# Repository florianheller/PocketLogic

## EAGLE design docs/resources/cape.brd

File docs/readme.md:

# Introduction
This is a documentation on how to use a [PocketBeagle](http://beagleboard.org/pocket) board to drive a [PlasticLogic](http://www.plasticlogic.com) ePaper display. 
I implemented a wearable prototype based on the 4.9" Lectum Display and started with the PlasticLogic [Ruddock 2](http://www.plasticlogic.com/products/evaluation-kits/kits-on-epson-platform/kits-4-9-inch-display/#1503061380699-f800df99-5e01) evaluation board. 
However, since my prototype was designed to be a wearable device, I had to move to a smaller form factor. 
As the platform is quite general-purpose, I share the information such that you can build your own one. 

# Prerequisites
For this tutorial I used the following hardware:
- PocketBeagle board ([link](http://beagleboard.org/pocket))
- 16Gb microSD-card (everything with 4Gb or more should do fine)
- PlasticLogic Hummingbird Z7.2 EPD Driver Board (C_HBZ7 / 301015) ([link](http://www.plasticlogic.com/products/evaluation-kits/kits-on-epson-platform/kits-4-9-inch-display/#1503061380699-f800df99-5e01))
- PlasticLogic 4.9" Lectum ePaper Display ([link](https://www.plasticlogic.com/products/displays/displays-with-epson/4-9-inch-display/))

This tutorial should work with all Epson S1D13541 EPD controller-based displays that are powered using the Hummingbird Z7.2 controller and connected using the 24-pin FPC connector. If in doubt, ask PlasticLogic first.  

# The Board
## Schematics 

[cape.sch](./resources/cape.sch)

## Board

[cape.brd](./resources/cape.brd)

I had my boards being manufactured by [Aisler](https://aisler.net). 

## BOM

| Part | Digikey Order Number |
| ---- | --- |
| XF2M-2415-1A  |  OR721CT-ND |
| USB			|  ED2989-ND  |
| R1, R2		|  RHM22DCT-ND|
| RNx			| 741X083101JPCT-ND|

# Preparing the PocketBeagle

First of all, you need to get you PocketBeagle running by flashing Linux onto a microSD card. 
Download the latest Debian image from the [beagleboard.org](http://beagleboard.org/latest-images) website. As the PocketBeagle does not have video output, we'll use the IoT-version without graphical desktop.
At the time of writing of this tutorial, the latest version was "Debian 9.5 2018-10-07 4GB SD IoT"

To flash the image, I use [Etcher](https://www.balena.io/etcher/). Just select the image and flash it onto your microSD card (all data on that card will be lost!). 

Once the OS is flashed, insert the microSD card into your PocketBeagle and connect it to your computer. On my Mac, it is reachable through IPs 192.168.6.2 or 192.168.7.2

SSH into your PocketBeagle using 
```ssh debian@192.168.7.2```
The default password is `temppwd' which you should change obviously.
 
### Optional: Re-partition the microSD-card to use its full capacity
The beagleboard images are set up to fit exactly on a 4Gb card. If you flash it onto a larger card, the remaining space will be left unused. 
If you want to use the additional space, you need to re-partition the card accordingly. See [this guide](https://elinux.org/Beagleboard:Expanding_File_System_Partition_On_A_microSD) for more info. 

### Install the required packages
```sudo apt-get install libfreetype6 ```

## Setting the pins to their intended use
The pins on the PocketBeagle can serve multiple purposes, from general purpose I/O to specific hardware capabilities. Their functionality is controlled through the config-pin command. For example, the Pin P1_08, which we will use for the SPI_CLK signal can have the following functionality:

```
debian@beaglebone:~$ config-pin -i P1_08
Pin name: P1_08
Function if no cape loaded: spi_sclk
Function if cape loaded: default gpio gpio_pu gpio_pd gpio_input spi_sclk uart i2c pwm pru_uart
Function information: spi0_sclk default gpio0_2 gpio0_2 gpio0_2 gpio0_2 spi0_sclk uart2_rxd i2c2_sda ehrpwm0a pru_uart
Kernel GPIO id: 2
PRU GPIO id: 34
```

To set the pins to their correct purpose automatically at boot time, we will use the same procedure as described [here](https://gist.github.com/pdp7/d4770a6ba17e666848796bf5cfd0caee)

## Configure pins at boot time

Create a file `/usr/bin/epdc-enable-pins.sh`

**sudo nano /usr/bin/epdc-enable-pins.sh**
```bash
#!/bin/bash
#EPDC Connector
config-pin P1_08 spi_sclk	#SPI_CLK
config-pin P1_10 spi		#SPI_MISO
config-pin P1_12 spi		#SPI_MOSI
config-pin P1_20 in			#HRDY
config-pin p1_32 in			#PMIC_POK
config-pin p1_33 in			#PMIC_FLT
config-pin p1_34 hi			#3V3_ENABLE
config-pin p1_36 lo			#BB_SLEEP

config-pin p2_08 hi			#HD/C
config-pin p2_09 i2c		#SCL
config-pin p2_10 hi			#SPI_CS
config-pin p2_11 i2c		#SDA
config-pin p2_17 hi			#RST
config-pin p2_18 hi+		#HIRQ
config-pin p2_19 lo			#PMIC_EN
config-pin p2_20 lo			#HVSW_CTRL

```

**sudo chmod 755 /usr/bin/epdc-enable-pins.sh**

Create a system service file `/lib/systemd/system/epdc-enable-pins.service`

**sudo nano /lib/systemd/system/epdc-enable-pins.service**
```
[Unit]
Description=Enable pins required for the ePaper display
After=generic-board-startup.service

[Service]
Type=simple
ExecStart=/usr/bin/epdc-enable-pins.sh

[Install]
WantedBy=multi-user.target
```
### Enable the new systemd service
**sudo systemctl daemon-reload**

**sudo systemctl enable epdc-enable-pins.service**

```
Created symlink /etc/systemd/system/multi-user.target.wants/epdc-enable-pins.service → /lib/systemd/system/epdc-enable-pins.service.
```

### Reboot and test
**sudo systemctl status epdc-enable-pins.service**
```
● epdc-enable-pins.service - Enable pins required for the ePaper display
   Loaded: loaded (/lib/systemd/system/epdc-enable-pins.service; enabled; vendor preset: enabled)
   Active: inactive (dead) since Sun 2018-10-07 16:41:02 UTC; 36s ago
  Process: 1531 ExecStart=/usr/bin/epdc-enable-pins.sh (code=exited, status=0/SUCCESS)
 Main PID: 1531 (code=exited, status=0/SUCCESS)

Oct 07 16:41:00 beaglebone systemd[1]: Started Enable pins required for the ePaper display.
```

# Copy the necessary configuration files
The epdc-app looks for the configuration files in the ```/boot/uboot```-folder. Depending on your configuration it might be more useful to place the files somewhere else and use softlinks (`ln -s`).
I copied the S049_T1.1 folder from this [Plastic Logic Repository)[https://github.com/plasticlogic/pl-bb-sd-card] and the following configuration files to /boot/uboot/: 

**`/boot/uboot/config.txt`**
```
display_type S049_T1.1

```

**`/boot/uboot/S049_T1.1/epdc.config`**
```
[version]
name = CONFIG_S049_T1.1

[display]
nvm = S1D13541
nvm_format = S1D13541
controller = S1D13541
temp_mode = MANUAL
instruction_code_file = "/boot/uboot/S049_T1.1/bin/Ecode.bin"
default_vcom = 4000
default_temp = 23
default_waveform = "/boot/uboot/S049_T1.1/display/waveform.bin"

[general]
driver_board = CHIFFCHAFF
control_system = BEAGLEBONE_BLACK
spi_port = 1
epdc_spi_port = 1
nvm_spi_port = 1
DISPLAY_SCRAMBLE_CONFIG	= 96

[vcom]
dac_x1				= 127	;   /* first DAC register value (25% of full scale) */
dac_y1				= 4172	;   /* corresponding first voltage in mV */
dac_x2				= 382	;   /* second DAC register value (75% of full scale) */
dac_y2				= 12490	;   /* corresponding second voltage in mV */
vgpos_mv 			= 25080	;   /* VGPOS in mV */
vgneg_mv 			=-32300	;   /* VGNEG in mV */
swing_ideal 	= 56886

[hv_hardware]
hv_config_vgl = -32300
hv_config_vgh =  25080
hv_config_vsh =  15000
vcom_driver = NULL
vcom_config = TPS65185
hv_driver = GPIO
hv_config = TPS65185
hv_timing = TPS65185
vcom_switch = GPIO
TOFFSET_VGL_ON	=	8
TOFFSET_VSL_ON	=	2
TOFFSET_VSH_ON	=	11
TOFFSET_VGH_ON	=	3
TOFFSET_VGH_OFF	=	0
TOFFSET_VSH_OFF	=	0
TOFFSET_VSL_OFF	=	0
TOFFSET_VGL_OFF	=	0
```

# Install the EPDC-App compiled for the PocketBeagle
Check the [pl-bb-epd companion repository](https://github.com/florianheller/pl-bb-epd/) for the latest version.
You can download a pre-compiled version that works on the Debian 9.5 image mentioned at the beginning of this document. [epdc-app](./resources/epdc-app)
## Test it

```
debian@beaglebone:~$ ./epdc-app -start_epdc 0 1
configparser     DISPLAYTYPE: S049_T1.1
configparser     version - CONFIG_S049_T1.1

configparser     Interface: SPI
s1d13541_controller Using HDC GPIO
configparser     No register settings specified in the configuration file.
main             load_nvm_content?: 0
s1d135xx         Product code: 0x0053
s1d13541_controller Ready 360x240
generic_epdc     epdc_init: stat: 0
tps65185         Version: 1.2.5
tps65185         tps65185_apply_timings - not yet implemented
nvm              Used nvm format (1) does not support load waveform from nvm.
generic_epdc     NVM_FORMAT_S1D13541 does not support Wf loading from NVM
generic_epdc     Loading wflib: /boot/uboot/S049_T1.1/display/waveform.bin
generic_epdc     epdc_init: stat: 0
generic_epdc     Setting vcom: 4000
vcom             input: 4000, scaled: 4035, DAC reg: 0x7B
tps65185         calculate: 4000, 123
generic_epdc     epdc_init: stat: 0
generic_epdc     do_clear_update: stat: 0
generic_epdc     switch_hvs_on: stat: 0
generic_epdc     do_clear_update: stat: 0
generic_epdc     do_clear_update: stat: 0
generic_epdc     do_clear_update: stat: 0
generic_epdc     switch_hvs_off: stat: 0
generic_epdc     do_clear_update: stat: 0
```

## Update an image on the display
```
debian@beaglebone:~$ ./epdc-app -update_image /boot/uboot/S049_T1.1/img/dresden.png
configparser     DISPLAYTYPE: S049_T1.1
configparser     version - CONFIG_S049_T1.1

configparser     Interface: SPI
s1d13541_controller Using HDC GPIO
configparser     No register settings specified in the configuration file.
main             path: /boot/uboot/S049_T1.1/img/dresden.png
main             wfID: 1
main             updateMode: 0
main             updateCount: 1
main             waitTime: 0
main             vcomSwitch: 1
s1d135xx         BW
utils            filename /boot/uboot/S049_T1.1/img/dresden.png
utils            width 720, height 120, bit_depth 8, channels 1
generic_epdc     generic_update: stat: 0
generic_epdc     generic_update: stat: 0
generic_epdc     switch_hvs_on: stat: 0
generic_epdc     generic_update: stat: 0
generic_epdc     generic_update: stat: 0
generic_epdc     switch_hvs_off: stat: 0
generic_epdc     generic_update: stat: 0
```

# Enclosure
I designed a case for the assembly which I cut on the lasercutter using 3mm Plexiglass (Acrylic). 

# Legal & Acknowledgements
I am not associated to PlasticLogic in any way. I just use their hardware and received very good support while working on the adaptation of the EPD driver software. 

This tutorial is provided `as is'. I used the described setup and it worked fine, but I do not take any responsibility for potential problems that might arise when following this tutorial. 

This work was done at the Expertise Center for Digital Media at Hasselt University in Belgium. 
This work was partially funded by imec (ICON project SeRGIo), Flanders Make (ICON project OperatorKnowledge) and the Research Foundation - Flanders (FWO, project G0E7317N End-User Development of Intelligible Internet-of-Things Ob-jects and Applications)

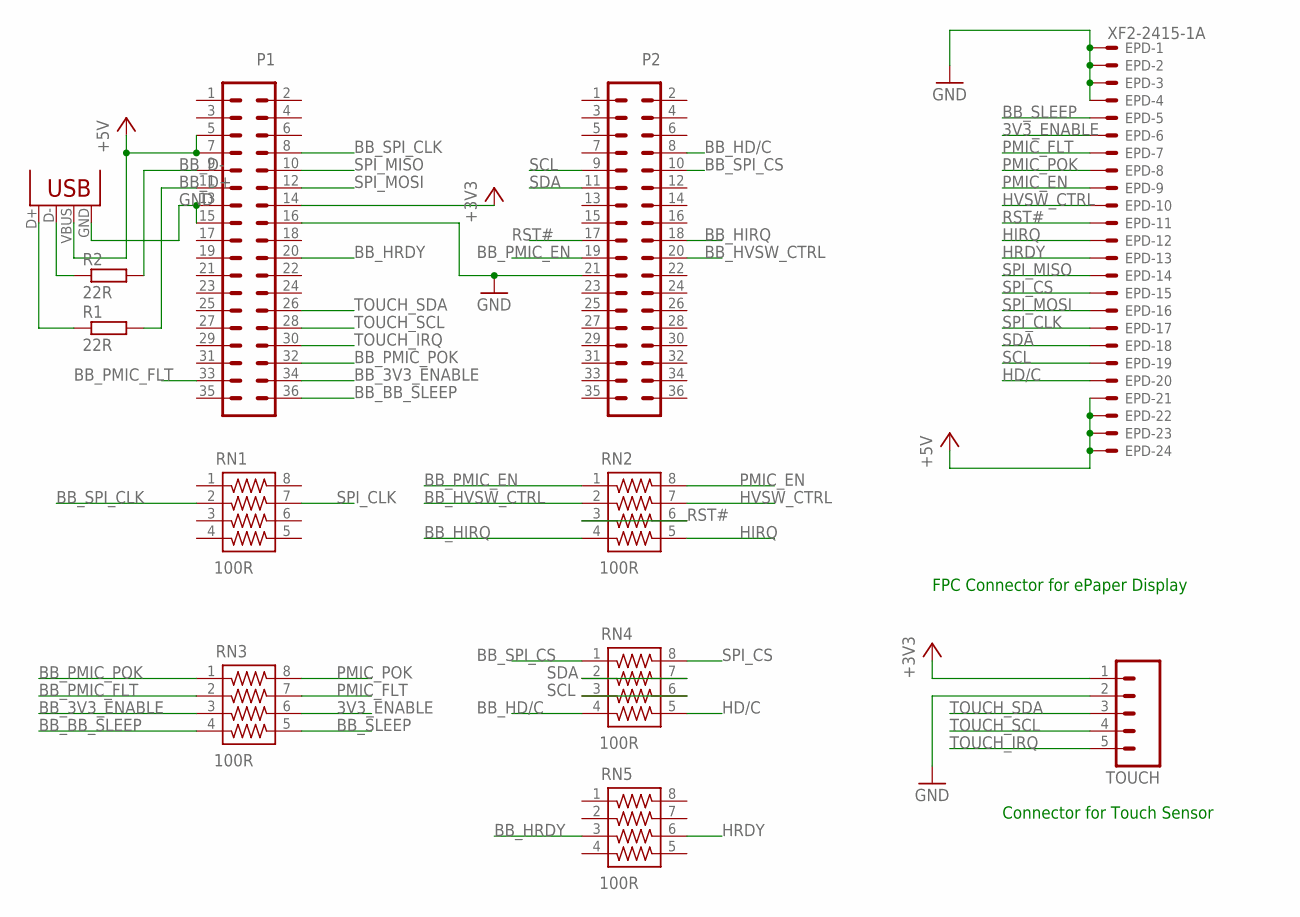
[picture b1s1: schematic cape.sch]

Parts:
EPD: XF2-2415-1A; XF2M-2415-1A
P1, P2: MA18-2
R1, R2: 22R; R0603
RN1, RN2, RN3, RN4, RN5: 100R; 741-8
TOUCH: M05PTH; 1X05
USB: USB-A-H

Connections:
3V3_ENABLE: EPD.6 (MS), RN3.6
+3V3: P1.14, TOUCH.1
+5V: EPD.21 (MS), EPD.22 (MS), EPD.23 (MS), EPD.24 (MS), P1.5, P1.7, USB.VBUS
BB_3V3_ENABLE: P1.34, RN3.3
BB_BB_SLEEP: P1.36, RN3.4
BB_D+: P1.11, R1.2
BB_D-: P1.9, R2.2
BB_HD/C: P2.8, RN4.4
BB_HIRQ: P2.18, RN2.4
BB_HRDY: P1.20, RN5.3
BB_HVSW_CTRL: P2.20, RN2.2
BB_PMIC_EN: P2.19, RN2.1
BB_PMIC_FLT: P1.33, RN3.2
BB_PMIC_POK: P1.32, RN3.1
BB_SLEEP: EPD.5 (MS), RN3.5
BB_SPI_CLK: P1.8, RN1.2
BB_SPI_CS: P2.10, RN4.1
D+: R1.1, USB.D+
D-: R2.1, USB.D-
GND: EPD.1 (MSV), EPD.2 (MS), EPD.3 (MS), EPD.4 (MS), P1.13, P1.15, P1.16, P2.21, TOUCH.2, USB.GND
HD/C: EPD.20 (MS), RN4.5
HIRQ: EPD.12 (MS), RN2.5
HRDY: EPD.13 (MS), RN5.6
HVSW_CTRL: EPD.10 (MS), RN2.7
PMIC_EN: EPD.9 (MS), RN2.8
PMIC_FLT: EPD.7 (MS), RN3.7
PMIC_POK: EPD.8 (MS), RN3.8
RST#: EPD.11 (MS), P2.17, RN2.3, RN2.6
SCL: EPD.19 (MS), P2.9, RN4.3, RN4.6
SDA: EPD.18 (MS), P2.11, RN4.2, RN4.7
SPI_CLK: EPD.17 (MS), RN1.7
SPI_CS: EPD.15 (MS), RN4.8
SPI_MISO: EPD.14 (MS), P1.10
SPI_MOSI: EPD.16 (MS), P1.12
TOUCH_IRQ: P1.30, TOUCH.5
TOUCH_SCL: P1.28, TOUCH.4
TOUCH_SDA: P1.26, TOUCH.3

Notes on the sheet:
Connector for Touch Sensor
FPC Connector for ePaper Display

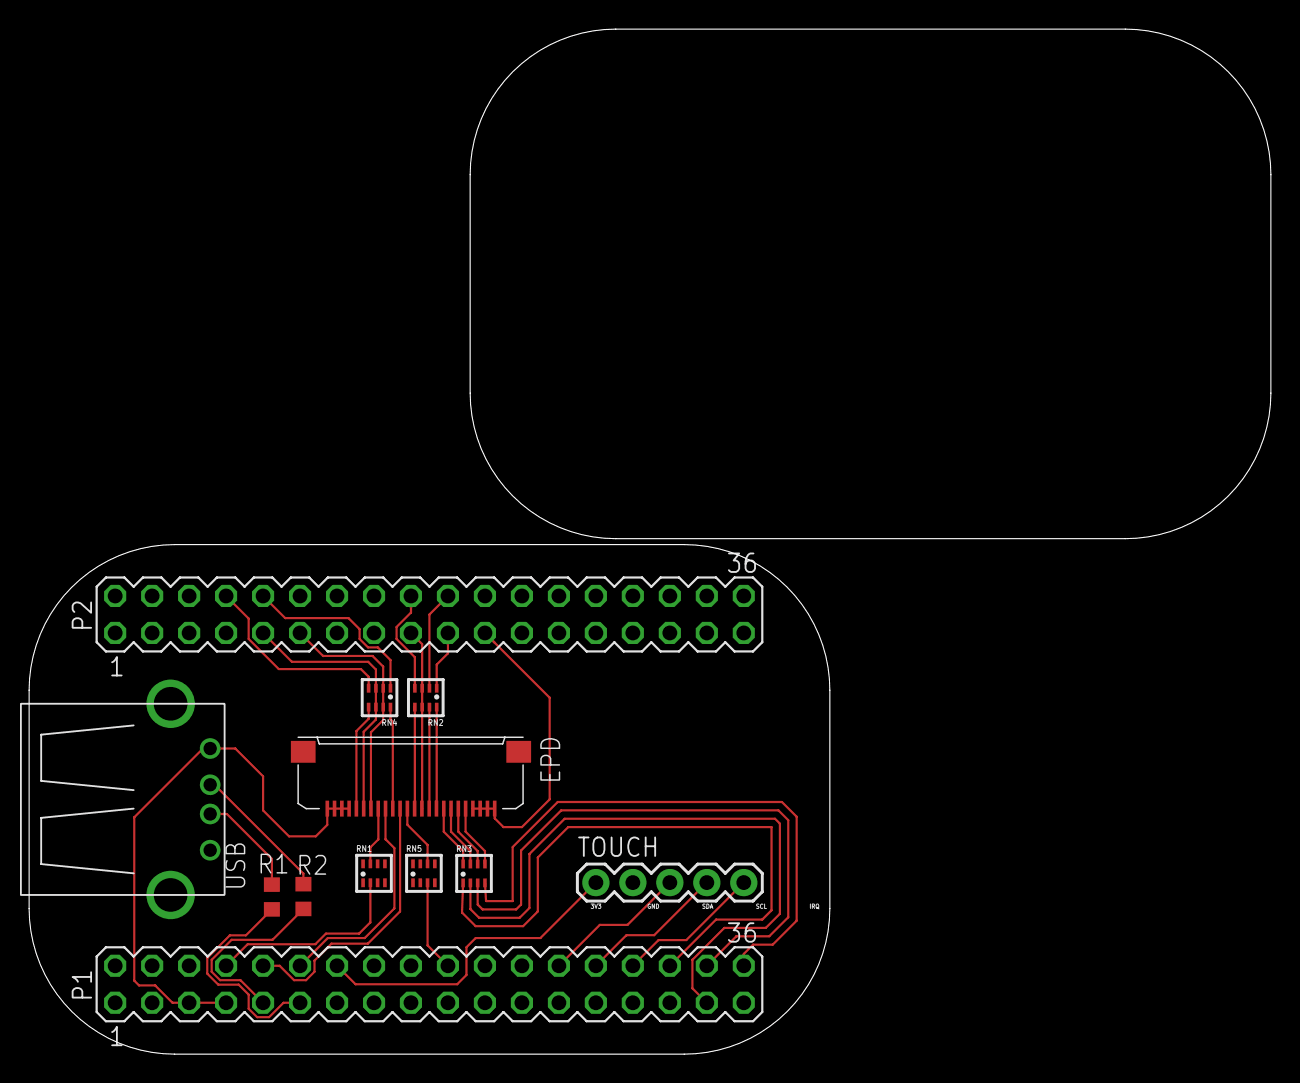
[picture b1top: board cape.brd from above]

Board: 2 copper layers, 85.3 x 70.4 mm, 12 parts (0 on the bottom side), 37 nets.

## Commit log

2019-05-31 Docs Folder
2019-05-31 Set theme jekyll-theme-slate
2019-05-31 Page is driven from docs folder
2019-05-31 Lots of documentation
2019-06-03 Formatting
2019-06-03 Some resources
2019-06-03 Added Resources
2019-06-03 Finished the description
2019-06-03 Board data
2019-06-03 Board details
2019-06-03 More details on the board
2019-06-03 Missing Space
2019-06-04 Consistency
2019-06-05 Casing

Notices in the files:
parts and their libraries:
SparkFun: Licensing: CC v3.0 Share-Alike You are welcome to use this library for commercial purposes.
resistor-array: Copyright (C) 2008, Bob Starr
